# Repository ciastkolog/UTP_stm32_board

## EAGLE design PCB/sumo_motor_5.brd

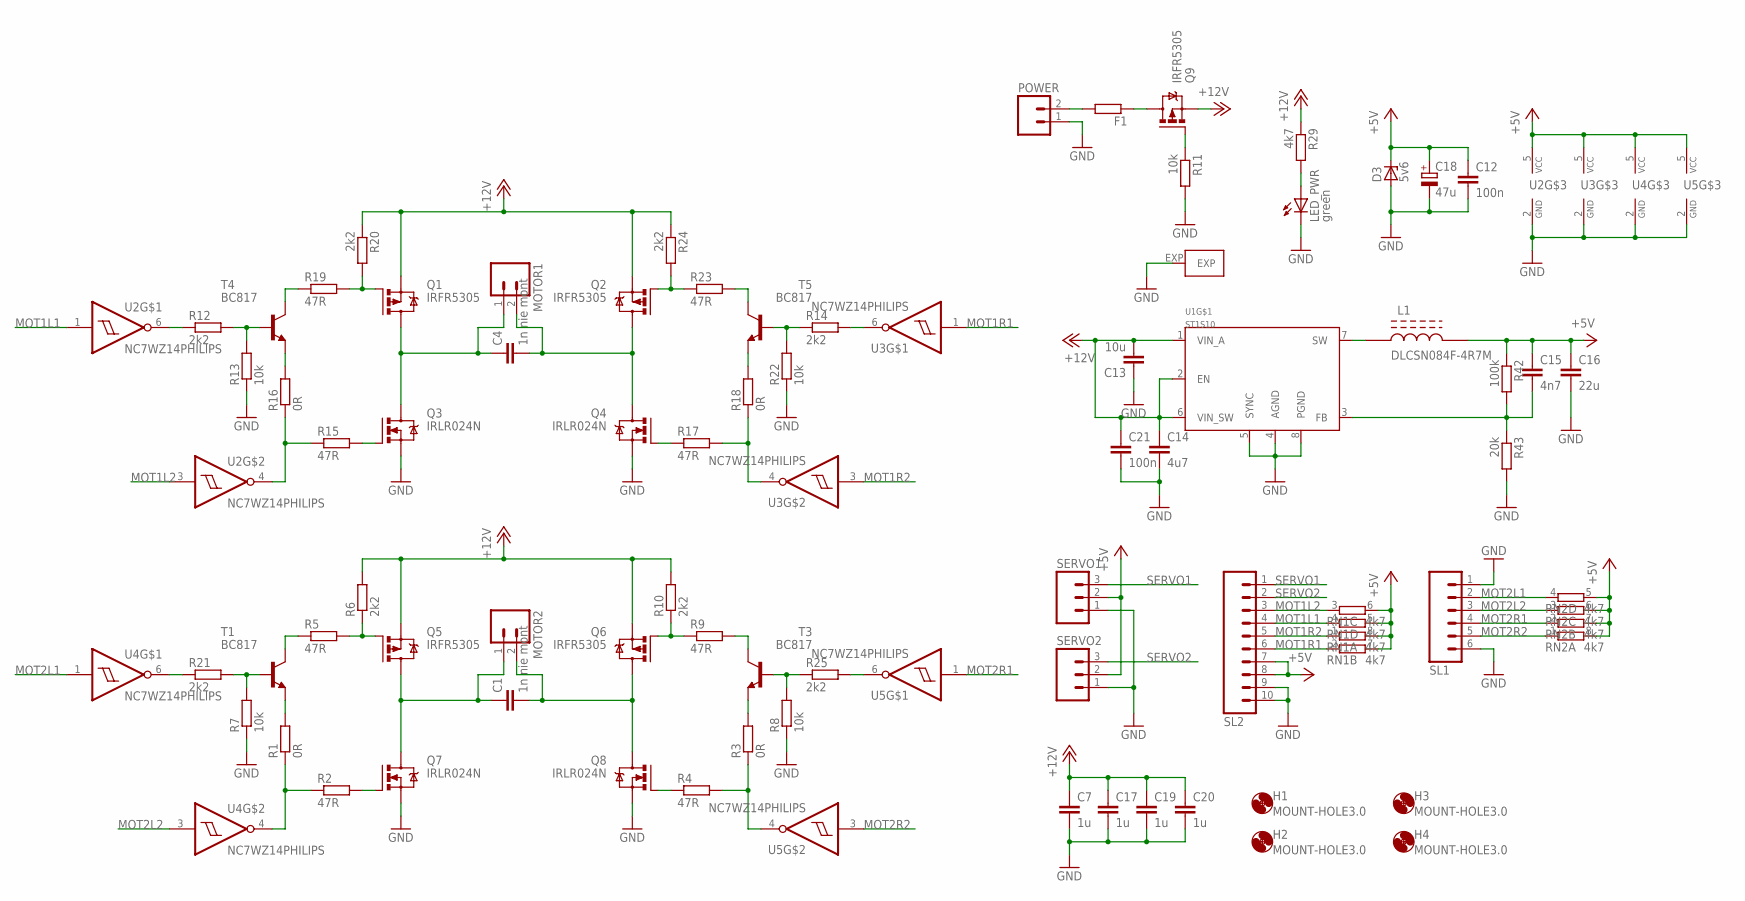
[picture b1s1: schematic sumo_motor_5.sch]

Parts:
C1, C4: 1n nie mont; C025-025X050
C7, C17, C19, C20: 1u; C0805
C12, C21: 100n; C0805
C13: 10u; C1206K
C14: 4u7; C0805
C15: 4n7; C0805
C16: 22u; C0805
C18: 47u; SMC_B
D3: 5v6; SMB
F1: R-EU_VMTA55; VMTA55
H1, H2, H3, H4: MOUNT-HOLE3.0; 3,0
L1: DLCSN084F-4R7M; CSN084F
LED_PWR: green; SML0805
MOTOR1, MOTOR2: M02; 02P
POWER: M02; 02P
Q1, Q2, Q5, Q6, Q9: IRFR5305; D-PAK_TO252AA
Q3, Q4, Q7, Q8: IRLR024N; D-PAK_TO252AA
R1, R3, R16, R18: 0R; R0603
R2, R4, R5, R9, R15, R17, R19, R23: 47R; R0603
R6, R10, R12, R14, R20, R21, R24, R25: 2k2; R0603
R7, R8, R11, R13, R22: 10k; R0603
R29: 4k7; R0603
R42: 100k; R0603
R43: 20k; R0603
RN1, RN2: 4k7; CAT16XXX
SERVO1, SERVO2: M03; 03P
SL1: M06; 06P
SL2: M10; 10P
T1, T3, T4, T5: BC817; SOT23-BEC
U1: ST1S10; HSOP8
U2, U3, U4, U5: NC7WZ14PHILIPS; SOT363_PHILIPS

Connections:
+5V: C12.1, C15.1, C16.1, C18.+, D3.C, L1.2, R42.1, RN1.5 (2), RN1.6 (2), RN1.7 (2), RN1.8 (2), RN2.5 (2), RN2.6 (2), RN2.7 (2), RN2.8 (2), SERVO1.2, SERVO2.2, SL2.7, SL2.8, U2.5 (VCC), U3.5 (VCC), U4.5 (VCC), U5.5 (VCC)
+12V: C7.1, C13.2, C14.1, C17.1, C19.1, C20.1, C21.1, Q1.3 (S), Q2.3 (S), Q5.3 (S), Q6.3 (S), Q9.3 (S), R6.2, R10.2, R20.1, R24.1, R29.1, U1.1 (VIN_A), U1.2 (EN), U1.6 (VIN_SW)
GND: C7.2, C12.2, C13.1, C14.2, C16.2, C17.2, C18.-, C19.2, C20.2, C21.2, D3.A, LED_PWR.C, POWER.1, Q3.3 (S), Q4.3 (S), Q7.3 (S), Q8.3 (S), R7.1, R8.1, R11.2, R13.1, R22.1, R43.2, SERVO1.1, SERVO2.1, SL1.1, SL1.6, SL2.9, SL2.10, U1.4 (AGND), U1.5 (SYNC), U1.8 (PGND), U1.EXP, U2.2 (GND), U3.2 (GND), U4.2 (GND), U5.2 (GND)
MOT1L1: RN1.4 (1), SL2.4, U2.1 (I)
MOT1L2: RN1.3 (1), SL2.3, U2.3 (I)
MOT1R1: RN1.2 (1), SL2.6, U3.1 (I)
MOT1R2: RN1.1, SL2.5, U3.3 (I)
MOT2L1: RN2.4 (1), SL1.2, U4.1 (I)
MOT2L2: RN2.3 (1), SL1.3, U4.3 (I)
MOT2R1: RN2.2 (1), SL1.4, U5.1 (I)
MOT2R2: RN2.1, SL1.5, U5.3 (I)
unnamed: R5.1, T1.C
unnamed: C1.1, MOTOR2.1, Q5.4 (D), Q7.4 (D)
unnamed: C1.2, MOTOR2.2, Q6.4 (D), Q8.4 (D)
unnamed: R19.1, T4.C
unnamed: R7.2, R21.2, T1.B
unnamed: Q5.1 (G), R5.2, R6.1
unnamed: Q6.1 (G), R9.1, R10.1
unnamed: R21.1, U4.6 (O)
unnamed: R1.2, T1.E
unnamed: R1.1, R2.1, U4.4 (O)
unnamed: Q3.1 (G), R15.2
unnamed: R16.2, T4.E
unnamed: Q7.1 (G), R2.2
unnamed: C4.1, MOTOR1.1, Q1.4 (D), Q3.4 (D)
unnamed: C4.2, MOTOR1.2, Q2.4 (D), Q4.4 (D)
unnamed: Q1.1 (G), R19.2, R20.2
unnamed: Q2.1 (G), R23.1, R24.2
unnamed: Q4.1 (G), R17.1
unnamed: R17.2, R18.1, U3.4 (O)
unnamed: R12.2, R13.2, T4.B
unnamed: R12.1, U2.6 (O)
unnamed: R18.2, T5.E
unnamed: R14.2, U3.6 (O)
unnamed: F1.2, POWER.2
unnamed: F1.1, Q9.4 (D)
unnamed: LED_PWR.A, R29.2
unnamed: Q8.1 (G), R4.1
unnamed: R3.1, R4.2, U5.4 (O)
unnamed: R3.2, T3.E
unnamed: R9.2, T3.C
unnamed: R8.2, R25.1, T3.B
unnamed: R25.2, U5.6 (O)
unnamed: L1.1, U1.7 (SW)
unnamed: C15.2, R42.2, R43.1, U1.3 (FB)
unnamed: Q9.1 (G), R11.1
unnamed: R23.2, T5.C
unnamed: R15.1, R16.1, U2.4 (O)
unnamed: R14.1, R22.2, T5.B
SERVO1: SERVO1.3, SL2.1
SERVO2: SERVO2.3, SL2.2

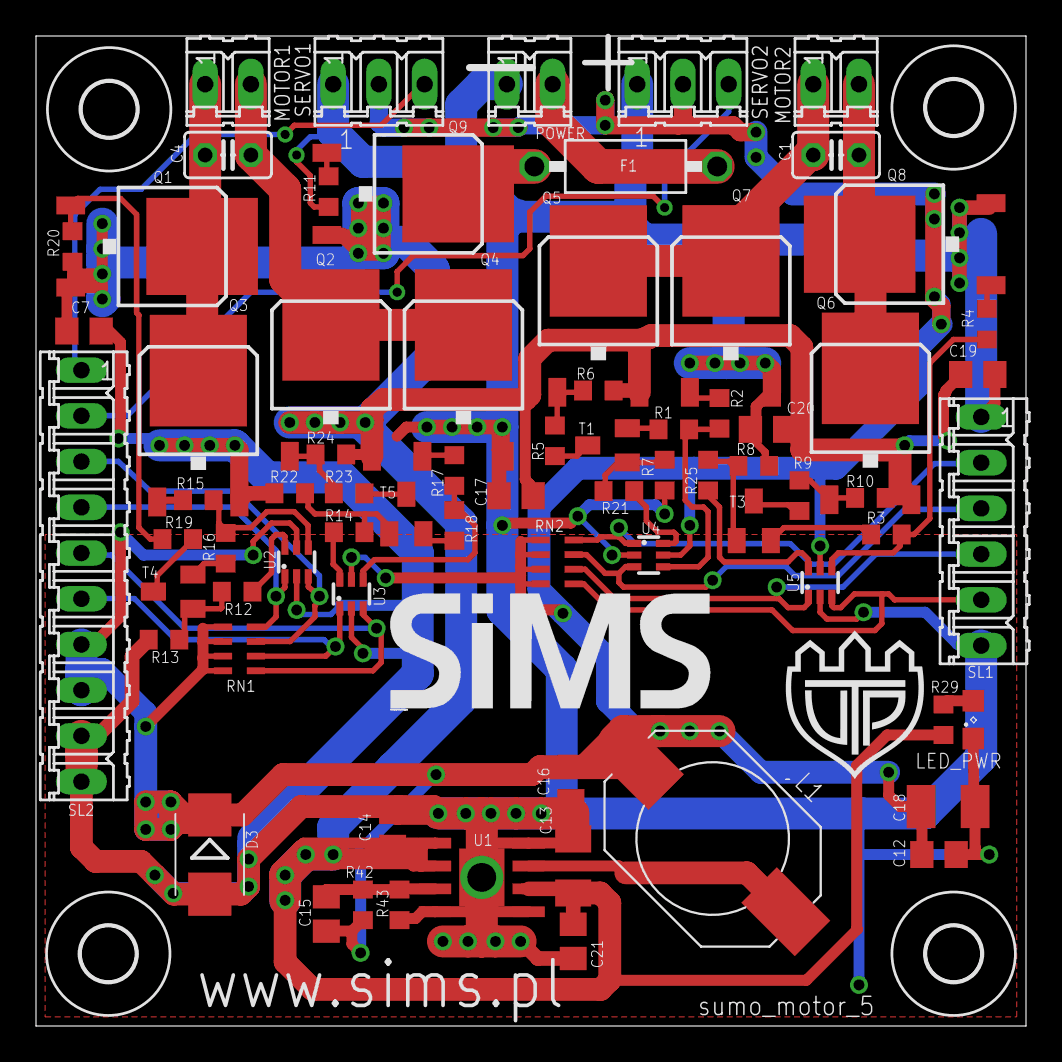
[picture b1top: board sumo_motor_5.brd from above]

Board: 2 copper layers, 55.0 x 55.0 mm, 78 parts (0 on the bottom side), 51 nets.

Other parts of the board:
U$1: SIMS_07
U$2: UTP_016

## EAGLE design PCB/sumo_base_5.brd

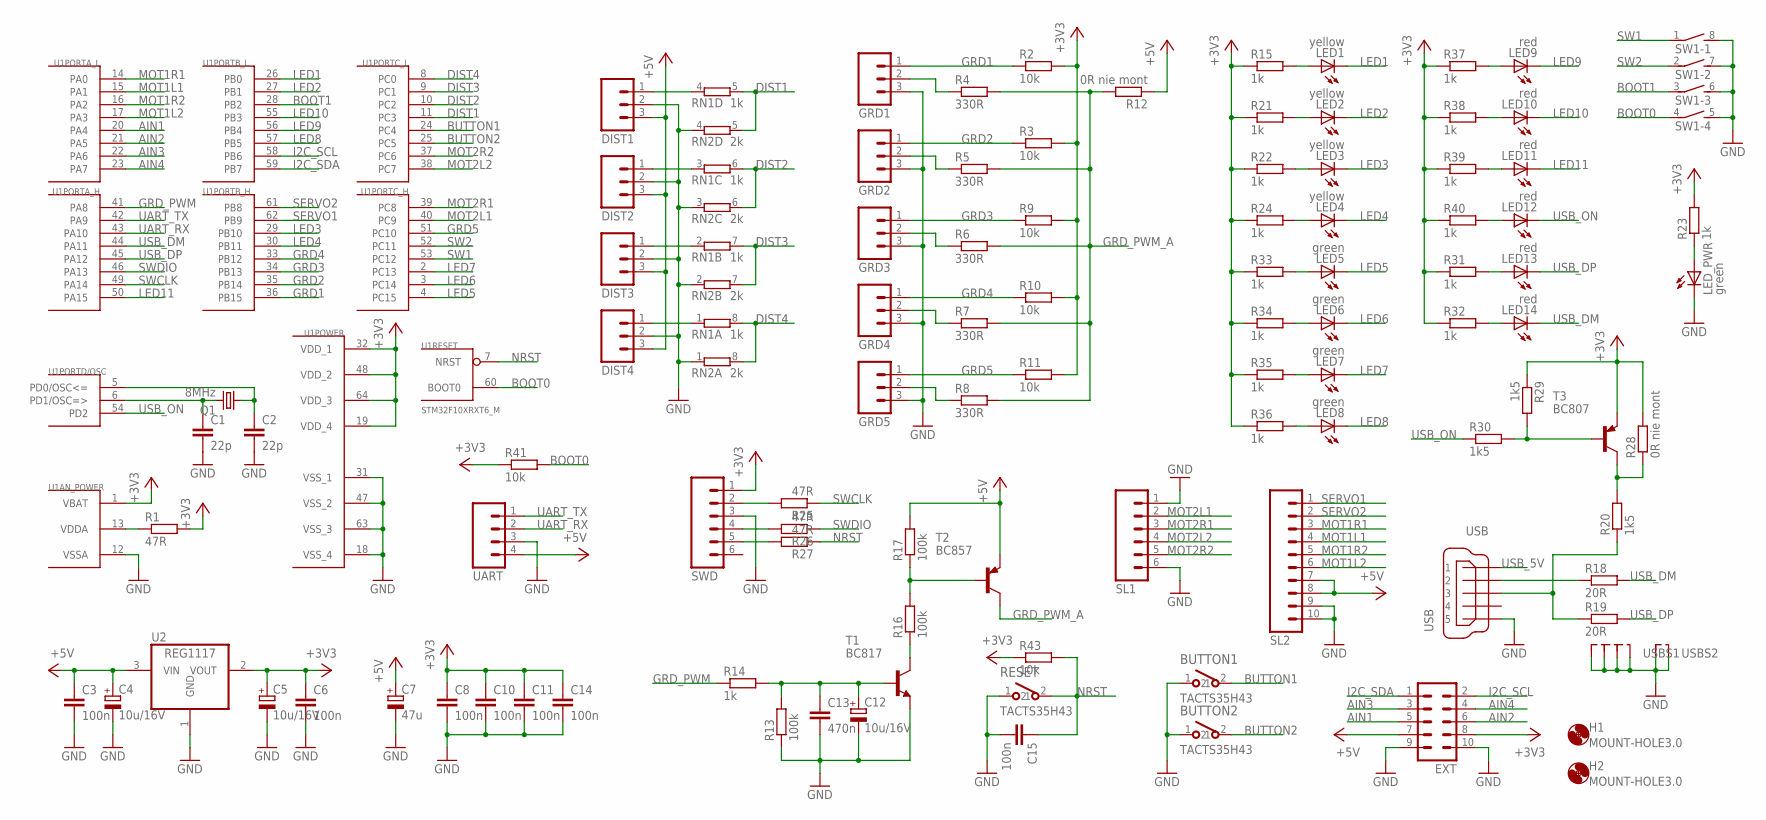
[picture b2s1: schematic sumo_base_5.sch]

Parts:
BUTTON1, BUTTON2: TACTS35H43
C1, C2: 22p; C0603
C3, C6, C8, C10, C11, C14, C15: 100n; C0603
C4, C5, C12: 10u/16V; SMC_A
C7: 47u; SMC_B
C13: 470n; C0603
DIST1, DIST2, DIST3, DIST4: M03; 03P
EXT: MA05-2
GRD1, GRD2, GRD3, GRD4, GRD5: M03; 03P
H1, H2: MOUNT-HOLE3.0; 3,0
LED1, LED2, LED3, LED4: yellow; SML0805
LED5, LED6, LED7, LED8: green; SML0805
LED9, LED10, LED11, LED12, LED13, LED14: red; SML0805
LED_PWR: green; SML0805
Q1: 8MHz; HC49/S
R1, R25, R26, R27: 47R; R0603
R2, R3, R9, R10, R11, R41, R43: 10k; R0603
R4, R5, R6, R7, R8: 330R; R0603
R12, R28: 0R nie mont; R0603
R13, R16, R17: 100k; R0603
R14, R15, R21, R22, R23, R24, R31, R32, R33, R34, R35, R36, R37, R38, R39, R40: 1k; R0603
R18, R19: 20R; R0603
R20, R29, R30: 1k5; R0603
RESET: TACTS35H43
RN1: 1k; CAT16XXX
RN2: 2k; CAT16XXX
SL1: M06; 06P
SL2: M10; 10P
SW1: DIP04S
SWD: M06; 06P
T1: BC817; SOT23-BEC
T2: BC857; SOT23-BEC
T3: BC807; SOT23-BEC
U1: STM32F10XRXT6_M; FP64E
U2: REG1117; SOT223
UART: M04; 04P
USB: USB; MX47346

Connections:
+3V3: C5.+, C6.1, C8.1, C10.1, C11.1, C14.1, EXT.8, R1.2, R2.2, R3.2, R9.2, R10.2, R11.2, R15.1, R21.1, R22.1, R23.2, R24.1, R28.2, R29.1, R31.1, R32.1, R33.1, R34.1, R35.1, R36.1, R37.1, R38.1, R39.1, R40.1, R41.1, R43.1, SWD.1, T3.E, U1.1 (VBAT), U1.19 (VDD_4), U1.32 (VDD_1), U1.48 (VDD_2), U1.64 (VDD_3), U2.2 (VOUT)
+5V: C3.1, C4.+, C7.+, DIST1.3, DIST2.3, DIST3.3, DIST4.3, EXT.7, R12.1, R17.2, SL2.7, SL2.8, T2.E, U2.3 (VIN), UART.4
AIN1: EXT.5, U1.20 (PA4)
AIN2: EXT.6, U1.21 (PA5)
AIN3: EXT.3, U1.22 (PA6)
AIN4: EXT.4, U1.23 (PA7)
BOOT0: R41.2, SW1.4 (1), U1.60 (BOOT0)
BOOT1: SW1.3 (1), U1.28 (PB2)
BUTTON1: BUTTON1.2, U1.24 (PC4)
BUTTON2: BUTTON2.2, U1.25 (PC5)
DIST1: RN1.5 (2), RN2.5 (2), U1.11 (PC3)
DIST2: RN1.6 (2), RN2.6 (2), U1.10 (PC2)
DIST3: RN1.7 (2), RN2.7 (2), U1.9 (PC1)
DIST4: RN1.8 (2), RN2.8 (2), U1.8 (PC0)
GND: BUTTON1.1, BUTTON2.1, C1.2, C2.2, C3.2, C4.-, C5.-, C6.2, C7.-, C8.2, C10.2, C11.2, C12.-, C13.2, C14.2, C15.2, DIST1.2, DIST2.2, DIST3.2, DIST4.2, EXT.9, EXT.10, GRD1.3, GRD2.3, GRD3.3, GRD4.3, GRD5.3, LED_PWR.C, R13.1, RESET.1, RN2.1, RN2.2 (1), RN2.3 (1), RN2.4 (1), SL1.1, SL1.6, SL2.9, SL2.10, SW1.5 (2), SW1.6 (2), SW1.7 (2), SW1.8 (2), SWD.3, T1.E, U1.12 (VSSA), U1.18 (VSS_4), U1.31 (VSS_1), U1.47 (VSS_2), U1.63 (VSS_3), U2.1 (GND), UART.3, USB.5, USB.M1 (S1), USB.M2 (S2), USB.M3 (S3), USB.M4 (S4), USB.M5 (S1), USB.M6 (S2)
GRD1: GRD1.1, R2.1, U1.36 (PB15)
GRD2: GRD2.1, R3.1, U1.35 (PB14)
GRD3: GRD3.1, R9.1, U1.34 (PB13)
GRD4: GRD4.1, R10.1, U1.33 (PB12)
GRD5: GRD5.1, R11.1, U1.51 (PC10)
GRD_PWM: R14.1, U1.41 (PA8)
GRD_PWM_A: R4.2, R5.2, R6.2, R7.2, R8.2, R12.2, T2.C
I2C_SCL: EXT.2, U1.58 (PB6)
I2C_SDA: EXT.1, U1.59 (PB7)
LED1: LED1.C, U1.26 (PB0)
LED2: LED2.C, U1.27 (PB1)
LED3: LED3.C, U1.29 (PB10)
LED4: LED4.C, U1.30 (PB11)
LED5: LED5.C, U1.4 (PC15)
LED6: LED6.C, U1.3 (PC14)
LED7: LED7.C, U1.2 (PC13)
LED8: LED8.C, U1.57 (PB5)
LED9: LED9.C, U1.56 (PB4)
LED10: LED10.C, U1.55 (PB3)
LED11: LED11.C, U1.50 (PA15)
MOT1L1: SL2.4, U1.15 (PA1)
MOT1L2: SL2.6, U1.17 (PA3)
MOT1R1: SL2.3, U1.14 (PA0)
MOT1R2: SL2.5, U1.16 (PA2)
MOT2L1: SL1.2, U1.40 (PC9)
MOT2L2: SL1.4, U1.38 (PC7)
MOT2R1: SL1.3, U1.39 (PC8)
MOT2R2: SL1.5, U1.37 (PC6)
unnamed: R29.2, R30.2, T3.B
unnamed: R20.2, R28.1, T3.C
unnamed: LED_PWR.A, R23.1
unnamed: LED12.A, R40.2
unnamed: LED13.A, R31.2
unnamed: LED14.A, R32.2
unnamed: R25.2, SWD.2
unnamed: C2.1, Q1.1, U1.5 (PD0/OSC<=)
unnamed: C1.1, Q1.2, U1.6 (PD1/OSC=>)
unnamed: R1.1, U1.13 (VDDA)
unnamed: DIST1.1, RN1.4 (1)
unnamed: GRD3.2, R6.1
unnamed: DIST3.1, RN1.2 (1)
unnamed: DIST2.1, RN1.3 (1)
unnamed: DIST4.1, RN1.1
unnamed: GRD1.2, R4.1
unnamed: GRD2.2, R5.1
unnamed: GRD4.2, R7.1
unnamed: GRD5.2, R8.1
unnamed: C12.+, C13.1, R13.2, R14.2, T1.B
unnamed: LED1.A, R15.2
unnamed: LED2.A, R21.2
unnamed: LED3.A, R22.2
unnamed: LED4.A, R24.2
unnamed: LED5.A, R33.2
unnamed: LED6.A, R34.2
unnamed: LED7.A, R35.2
unnamed: LED8.A, R36.2
unnamed: R16.1, T1.C
unnamed: R16.2, R17.1, T2.B
unnamed: R18.1, USB.2
unnamed: R19.1, R20.1, USB.3
unnamed: LED9.A, R37.2
unnamed: LED10.A, R38.2
unnamed: LED11.A, R39.2
unnamed: R26.2, SWD.4
unnamed: R27.2, SWD.5
NRST: C15.1, R27.1, R43.2, RESET.2, U1.7 (NRST)
SERVO1: SL2.1, U1.62 (PB9)
SERVO2: SL2.2, U1.61 (PB8)
SW1: SW1.1, U1.53 (PC12)
SW2: SW1.2 (1), U1.52 (PC11)
SWCLK: R25.1, U1.49 (PA14)
SWDIO: R26.1, U1.46 (PA13)
UART_RX: U1.43 (PA10), UART.2
UART_TX: U1.42 (PA9), UART.1
USB_5V: USB.1
USB_DM: LED14.C, R18.2, U1.44 (PA11)
USB_DP: LED13.C, R19.2, U1.45 (PA12)
USB_ON: LED12.C, R30.1, U1.54 (PD2)

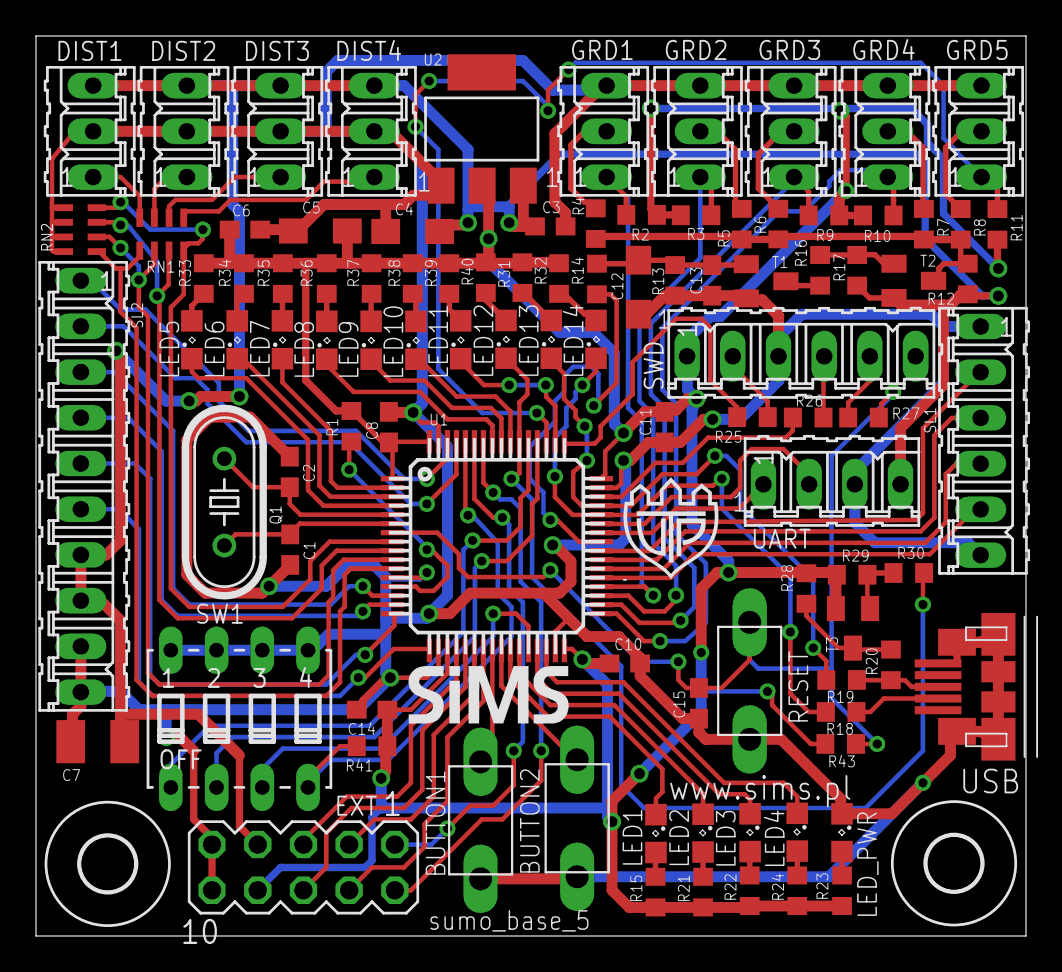
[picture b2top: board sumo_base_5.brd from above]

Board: 2 copper layers, 55.0 x 50.0 mm, 102 parts (0 on the bottom side), 92 nets.

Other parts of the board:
U$1: SIMS_035
U$2: UTP_011

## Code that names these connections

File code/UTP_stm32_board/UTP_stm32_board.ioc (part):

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Mcu.Name=STM32F103R(8-B)Tx
Mcu.Package=LQFP64
Mcu.UserName=STM32F103RBTx
PA10.Mode=Asynchronous
PA10.Signal=USART1_RX
PA13.Mode=Serial_Wire
PA13.Signal=SYS_JTMS-SWDIO
PA14.Mode=Serial_Wire
PA14.Signal=SYS_JTCK-SWCLK
PA15.GPIOParameters=PinState,GPIO_Label
PA15.GPIO_Label=LED11
PA15.PinState=GPIO_PIN_SET
PA15.Signal=GPIO_Output
PA9.Mode=Asynchronous
PA9.Signal=USART1_TX
PB0.GPIOParameters=PinState,GPIO_Label
PB0.GPIO_Label=LED1
PB0.PinState=GPIO_PIN_SET
PB0.Signal=GPIO_Output
PB1.GPIOParameters=PinState,GPIO_Label
PB1.GPIO_Label=LED2
PB1.PinState=GPIO_PIN_SET
PB1.Signal=GPIO_Output
PB10.GPIOParameters=PinState,GPIO_Label
PB10.GPIO_Label=LED3
PB10.PinState=GPIO_PIN_SET
PB10.Signal=GPIO_Output
PB11.GPIOParameters=PinState,GPIO_Label
PB11.GPIO_Label=LED4
PB11.PinState=GPIO_PIN_SET
PB11.Signal=GPIO_Output
PB2.GPIOParameters=GPIO_PuPd,GPIO_Label
PB2.GPIO_Label=SW3
PB2.GPIO_PuPd=GPIO_PULLUP
PB2.Signal=GPIO_Input
PB3.GPIOParameters=PinState,GPIO_Label
PB3.GPIO_Label=LED10
PB3.PinState=GPIO_PIN_SET
PB3.Signal=GPIO_Output
PB4.GPIOParameters=PinState,GPIO_Label
PB4.GPIO_Label=LED9
PB4.PinState=GPIO_PIN_SET
PB4.Signal=GPIO_Output
PB5.GPIOParameters=PinState,GPIO_Label
PB5.GPIO_Label=LED8
PB5.PinState=GPIO_PIN_SET
PB5.Signal=GPIO_Output
PC11.GPIOParameters=GPIO_PuPd,GPIO_Label
PC11.GPIO_Label=SW2
PC11.GPIO_PuPd=GPIO_PULLUP
PC11.Signal=GPIO_Input
PC12.GPIOParameters=GPIO_PuPd,GPIO_Label
PC12.GPIO_Label=SW1
PC12.GPIO_PuPd=GPIO_PULLUP
PC12.Signal=GPIO_Input
PC13-TAMPER-RTC.GPIOParameters=PinState,GPIO_Label
PC13-TAMPER-RTC.GPIO_Label=LED7
PC13-TAMPER-RTC.PinState=GPIO_PIN_SET
PC13-TAMPER-RTC.Signal=GPIO_Output
PC14-OSC32_IN.GPIOParameters=PinState,GPIO_Label
PC14-OSC32_IN.GPIO_Label=LED6
PC14-OSC32_IN.PinState=GPIO_PIN_SET
PC14-OSC32_IN.Signal=GPIO_Output
PC15-OSC32_OUT.GPIOParameters=PinState,GPIO_Label
PC15-OSC32_OUT.GPIO_Label=LED5
PC15-OSC32_OUT.PinState=GPIO_PIN_SET
PC15-OSC32_OUT.Signal=GPIO_Output
PC4.GPIOParameters=GPIO_PuPd,GPIO_Label
PC4.GPIO_Label=BUTTON1
PC4.GPIO_PuPd=GPIO_PULLUP
PC4.Signal=GPIO_Input
PC5.GPIOParameters=GPIO_PuPd,GPIO_Label
PC5.GPIO_Label=BUTTON2
PC5.GPIO_PuPd=GPIO_PULLUP
PC5.Signal=GPIO_Input
PD0-OSC_IN.Mode=HSE-External-Oscillator
PD0-OSC_IN.Signal=RCC_OSC_IN
PD1-OSC_OUT.Mode=HSE-External-Oscillator
PD1-OSC_OUT.Signal=RCC_OSC_OUT
PD2.GPIOParameters=PinState,GPIO_Label
PD2.GPIO_Label=USB_ON
PD2.PinState=GPIO_PIN_SET
PD2.Signal=GPIO_Output
RCC.SYSCLKFreq_VALUE=72000000
RCC.SYSCLKSource=RCC_SYSCLKSOURCE_PLLCLK
board=UTP_stm32_board

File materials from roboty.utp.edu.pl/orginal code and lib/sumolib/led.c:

/**
 * Funkcje obslugi diod LED, przyciskow i przelacznikow
 */

#include "stm32f10x.h"
#include "stm32f10x_gpio.h"
#include "stm32f10x_rcc.h"
#include "internal.h"

/**
 * Piny:
 * PB0 - LED1
 * PB1 - LED2
 * PB10 - LED3
 * PB11 - LED4
 * PC15 - LED5
 * PC14 - LED6
 * PC13 - LED7
 * PB5 - LED8
 * PB4 - LED9
 * PB3 - LED10
 * PA15 - LED11
 * PD2 - LED12 - USB_ON
 * PA12 - LED13 - USB_DP
 * PA11 - LED14 - USB_DM
 * PC4 - BUTTON1
 * PC5 - BUTTON2
 * PC12 - SW1
 * PC11 - SW2
 * PB2 - SW3 - BOOT1
 */

#define _LED_FIRST LED1
#if !_USB_ENABLE && _LED_EXT_ENABLE
#define _LED_LAST LED14
#else
#define _LED_LAST LED11
#endif

void switchLedInit() {
	// inicjalizacja portow przyciskow i przelacznikow
	GPIO_InitTypeDef GPIO_InitStructure;
	GPIO_InitStructure.GPIO_Speed = GPIO_Speed_50MHz;
	GPIO_InitStructure.GPIO_Mode = GPIO_Mode_IPU;
	GPIO_InitStructure.GPIO_Pin = GPIO_Pin_2;
	GPIO_Init(GPIOB, &GPIO_InitStructure);
	GPIO_InitStructure.GPIO_Pin = GPIO_Pin_4 | GPIO_Pin_5 | GPIO_Pin_11
			| GPIO_Pin_12;
	GPIO_Init(GPIOC, &GPIO_InitStructure);

	// wylaczenie pinow JTAGa
	GPIO_PinRemapConfig(GPIO_Remap_SWJ_JTAGDisable, ENABLE);

	// inicjalizacja portow diod LED
	GPIO_InitStructure.GPIO_Speed = GPIO_Speed_50MHz;
	GPIO_InitStructure.GPIO_Mode = GPIO_Mode_Out_PP;
	GPIO_InitStructure.GPIO_Pin = GPIO_Pin_15;
	GPIO_Init(GPIOA, &GPIO_InitStructure);
	GPIO_InitStructure.GPIO_Pin = GPIO_Pin_0 | GPIO_Pin_1 | GPIO_Pin_3
			| GPIO_Pin_4 | GPIO_Pin_5 | GPIO_Pin_10 | GPIO_Pin_11;
	GPIO_Init(GPIOB, &GPIO_InitStructure);
	GPIO_InitStructure.GPIO_Pin = GPIO_Pin_13 | GPIO_Pin_14 | GPIO_Pin_15;
	GPIO_Init(GPIOC, &GPIO_InitStructure);
#if !_USB_ENABLE && _LED_EXT_ENABLE
	GPIO_InitStructure.GPIO_Pin = GPIO_Pin_11 | GPIO_Pin_12;
	GPIO_Init(GPIOA, &GPIO_InitStructure);
	GPIO_InitStructure.GPIO_Pin = GPIO_Pin_2;
	GPIO_Init(GPIOD, &GPIO_InitStructure);
#endif
	// wygaszenie wszystkich
	int i;
	for (i = _LED_FIRST; i <= _LED_LAST; i++) {
		ledSet(i, LED_OFF);
	}
}

/**
 * Sprawdzenie czy przycisk jest nacisniety
 * buttonNumber - numer przycisku
 * zwraca 1 jesli tak, 0 jesli nie
 */
int buttonPressed(int buttonNumber) {
	switch (buttonNumber) {
	case BUTTON1:
		return !GPIO_ReadInputDataBit(GPIOC, GPIO_Pin_4);
	case BUTTON2:
		return !GPIO_ReadInputDataBit(GPIOC, GPIO_Pin_5);
	}
	return 0;
}

/**
 * Oczekiwanie na nacisniecie przycisku
 * buttonNumber - numer przycisku
 */
void waitForButton(int buttonNumber) {
	while (!buttonPressed(buttonNumber));
}

/**
 * Sprzwdzenie, czy przelacznik jest wlaczony
 * switchNumber - numer przelacznika
 * zwraca 1 jesli tak, 0 jesli nie
 */
int switchIsOn(int switchNumber) {
	switch (switchNumber) {
	case SWITCH1:
		return !GPIO_ReadInputDataBit(GPIOC, GPIO_Pin_12);
	case SWITCH2:
		return !GPIO_ReadInputDataBit(GPIOC, GPIO_Pin_11);
	case SWITCH3:
		return !GPIO_ReadInputDataBit(GPIOB, GPIO_Pin_2);
	}
	return 0;
}

/**
 * Zapalenie okreslonej diody
 * ledNumber - numer diody
 */
void ledOn(int ledNumber) {
	ledSet(ledNumber, LED_ON);
}

/**
 * Gaszenie okreslonej diody
 * ledNumber - numer diody
 */
void ledOff(int ledNumber) {
	ledSet(ledNumber, LED_OFF);
}

/**
 * Ustawienie stanu okreslonej diody
 * ledNumber - numer diody
 * ledState - stan diody 0 - zgaszona, 1 - zapalona
 */
void ledSet(int ledNumber, int ledState) {
	switch (ledNumber) {
	case LED1:
		GPIO_WriteBit(GPIOB, GPIO_Pin_0, !ledState);
		break;
	case LED2:
		GPIO_WriteBit(GPIOB, GPIO_Pin_1, !ledState);
		break;
	case LED3:
		GPIO_WriteBit(GPIOB, GPIO_Pin_10, !ledState);
		break;
	case LED4:
		GPIO_WriteBit(GPIOB, GPIO_Pin_11, !ledState);
		break;
	case LED5:
		GPIO_WriteBit(GPIOC, GPIO_Pin_15, !ledState);
		break;
	case LED6:
		GPIO_WriteBit(GPIOC, GPIO_Pin_14, !ledState);
		break;
	case LED7:
		GPIO_WriteBit(GPIOC, GPIO_Pin_13, !ledState);
		break;
	case LED8:
		GPIO_WriteBit(GPIOB, GPIO_Pin_5, !ledState);
		break;
	case LED9:
		GPIO_WriteBit(GPIOB, GPIO_Pin_4, !ledState);
		break;
	case LED10:
		GPIO_WriteBit(GPIOB, GPIO_Pin_3, !ledState);
		break;
	case LED11:
		GPIO_WriteBit(GPIOA, GPIO_Pin_15, !ledState);
		break;
#if !_USB_ENABLE && _LED_EXT_ENABLE
		case LED12:
		GPIO_WriteBit(GPIOD, GPIO_Pin_2, !ledState);
		break;
		case LED13:
		GPIO_WriteBit(GPIOA, GPIO_Pin_12, !ledState);
		break;
		case LED14:
		GPIO_WriteBit(GPIOA, GPIO_Pin_11, !ledState);
		break;
#endif
	}

}

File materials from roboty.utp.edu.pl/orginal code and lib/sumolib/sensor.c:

/**
 * Funkcje obslugi czujnikow
 */
#include "stm32f10x.h"
#include "stm32f10x_gpio.h"
#include "stm32f10x_rcc.h"
#include "stm32f10x_tim.h"
#include "stm32f10x_adc.h"
#include "stm32f10x_dma.h"
#include "internal.h"
/**
 * Piny:
 * PC3 - DIST1 - IN13
 * PC2 - DIST2 - IN12
 * PC1 - DIST3 - IN11
 * PC0 - DIST4 - IN10
 * PA4 - AIN1 - IN4
 * PA5 - AIN2 - IN3
 * PA6 - AIN3 - IN2
 * PA7 - AIN4 - IN1
 * PB15 - GRD1
 * PB14 - GRD2
 * PB13 - GRD3
 * PB12 - GRD4
 * PC10 - GRD5
 * PA8- GRD_PWM - TIM1_CH1
 */
#define ADC1_DR_Address    ((uint32_t)0x4001244C)
#if _USE_EXT_DIST
#define _CHANNEL_NUMBER 8
#else
#define _CHANNEL_NUMBER 4
#endif
// wartosci pomiarow
__IO uint16_t distValues[_CHANNEL_NUMBER];
// czulosc czujnikow w %
__IO uint8_t grdSensivity = 100;
// licznik na potrzeby programowego PWMa
__IO uint16_t grdSensCounter = 0;

void sensorInit() {

	// konfiguracja portow - DIST
	GPIO_InitTypeDef GPIO_InitStructure;
	GPIO_InitStructure.GPIO_Mode = GPIO_Mode_AIN;
	GPIO_InitStructure.GPIO_Pin = GPIO_Pin_0 | GPIO_Pin_1 | GPIO_Pin_2
			| GPIO_Pin_3;
	GPIO_Init(GPIOC, &GPIO_InitStructure);
#if _DIST_EXT_ENABLE
	GPIO_InitStructure.GPIO_Pin = GPIO_Pin_4 | GPIO_Pin_5 | GPIO_Pin_6 | GPIO_Pin_7;
	GPIO_Init(GPIOA, &GPIO_InitStructure);
#endif

	// konfiguracja DMA
	DMA_DeInit(DMA1_Channel1);
	DMA_InitTypeDef DMA_InitStructure;
	DMA_InitStructure.DMA_PeripheralBaseAddr = ADC1_DR_Address;
	DMA_InitStructure.DMA_MemoryBaseAddr = (uint32_t) & distValues;
	DMA_InitStructure.DMA_DIR = DMA_DIR_PeripheralSRC;
	DMA_InitStructure.DMA_BufferSize = _CHANNEL_NUMBER;
	DMA_InitStructure.DMA_PeripheralInc = DMA_PeripheralInc_Disable;
	DMA_InitStructure.DMA_MemoryInc = DMA_MemoryInc_Enable;
	DMA_InitStructure.DMA_PeripheralDataSize = DMA_PeripheralDataSize_HalfWord;
	DMA_InitStructure.DMA_MemoryDataSize = DMA_MemoryDataSize_HalfWord;
	DMA_InitStructure.DMA_Mode = DMA_Mode_Circular;
	DMA_InitStructure.DMA_Priority = DMA_Priority_High;
	DMA_InitStructure.DMA_M2M = DMA_M2M_Disable;
	DMA_Init(DMA1_Channel1, &DMA_InitStructure);
	DMA_Cmd(DMA1_Channel1, ENABLE);

	// konfiguracja ADC
	ADC_InitTypeDef ADC_InitStructure;
	ADC_InitStructure.ADC_Mode = ADC_Mode_Independent;
	ADC_InitStructure.ADC_ScanConvMode = ENABLE;
	ADC_InitStructure.ADC_ContinuousConvMode = ENABLE;
	ADC_InitStructure.ADC_ExternalTrigConv = ADC_ExternalTrigConv_None;
	ADC_InitStructure.ADC_DataAlign = ADC_DataAlign_Right;
	ADC_InitStructure.ADC_NbrOfChannel = _CHANNEL_NUMBER;
	ADC_Init(ADC1, &ADC_InitStructure);

	ADC_RegularChannelConfig(ADC1, ADC_Channel_13, 1, ADC_SampleTime_55Cycles5);
	ADC_RegularChannelConfig(ADC1, ADC_Channel_12, 2, ADC_SampleTime_55Cycles5);
	ADC_RegularChannelConfig(ADC1, ADC_Channel_11, 3, ADC_SampleTime_55Cycles5);
	ADC_RegularChannelConfig(ADC1, ADC_Channel_10, 4, ADC_SampleTime_55Cycles5);
#if _DIST_EXT_ENABLE
	ADC_RegularChannelConfig(ADC1, ADC_Channel_4, 5, ADC_SampleTime_55Cycles5);
	ADC_RegularChannelConfig(ADC1, ADC_Channel_3, 6, ADC_SampleTime_55Cycles5);
	ADC_RegularChannelConfig(ADC1, ADC_Channel_2, 7, ADC_SampleTime_55Cycles5);
	ADC_RegularChannelConfig(ADC1, ADC_Channel_1, 8, ADC_SampleTime_55Cycles5);
#endif

	// uruchomienie przetwarzania
	ADC_DMACmd(ADC1, ENABLE);
	ADC_Cmd(ADC1, ENABLE);
	ADC_ResetCalibration(ADC1);
	while (ADC_GetResetCalibrationStatus(ADC1))
		;
	ADC_StartCalibration(ADC1);
	while (ADC_GetCalibrationStatus(ADC1))
		;
	ADC_SoftwareStartConvCmd(ADC1, ENABLE);

	// konfiguracja portow - GRD
	GPIO_InitStructure.GPIO_Speed = GPIO_Speed_50MHz;
	GPIO_InitStructure.GPIO_Mode = GPIO_Mode_IPU;
	GPIO_InitStructure.GPIO_Pin = GPIO_Pin_12 | GPIO_Pin_13 | GPIO_Pin_14
			| GPIO_Pin_15;
	GPIO_Init(GPIOB, &GPIO_InitStructure);
	GPIO_InitStructure.GPIO_Pin = GPIO_Pin_10;
	GPIO_Init(GPIOC, &GPIO_InitStructure);
	GPIO_InitStructure.GPIO_Mode = GPIO_Mode_Out_PP;
	GPIO_InitStructure.GPIO_Pin = GPIO_Pin_8;
	GPIO_Init(GPIOA, &GPIO_InitStructure);
	GPIO_SetBits(GPIOA, GPIO_Pin_8);
}

/**
 * Pobranie wartosci czujnika w mv
 * distNumber - numer czujnika
 */
int distValue(int distNumber) {
	int value = 0;
	switch (distNumber) {
	case DIST1:
		value = distValues[0];
		break;
	case DIST2:
		value = distValues[1];
		break;
	case DIST3:
		value = distValues[2];
		break;
	case DIST4:
		value = distValues[3];
		break;
#if _DIST_EXT_ENABLE
		case DIST5:
		value = distValues[4];
		break;
		case DIST6:
		value = distValues[5];
		break;
		case DIST7:
		value = distValues[6];
		break;
		case DIST8:
		value = distValues[7];
		break;
#endif
	}
	return (value * 807L) / 1000;
}

/**
 * Sprawdzenie, czy czujnik widzi biala linie
 * grdNumber - numer czujnika
 */
int grdDetected(int grdNumber) {
	switch (grdNumber) {
	case GRD1:
		return !GPIO_ReadInputDataBit(GPIOB, GPIO_Pin_15);
	case GRD2:
		return !GPIO_ReadInputDataBit(GPIOB, GPIO_Pin_14);
	case GRD3:
		return !GPIO_ReadInputDataBit(GPIOB, GPIO_Pin_13);
	case GRD4:
		return !GPIO_ReadInputDataBit(GPIOB, GPIO_Pin_12);
	case GRD5:
		return !GPIO_ReadInputDataBit(GPIOC, GPIO_Pin_10);
	}
	return 0;
}

/**
 * Ustawienie czulosci czujnikow, w zakresie 0-100%
 * sensivity czulosc
 */
void grdSetSensivity(int sensivity) {
	if (sensivity < 0) {
		sensivity = 0;
	} else if (sensivity > 100) {
		sensivity = 100;
	}
	grdSensivity = sensivity;
}

void sensorSystickInterrupt() {
	// programowy PWM do jasnosci diod czujnikow podloza
	grdSensCounter++;
	// przelaczanie
	if (grdSensivity < 100) {
		if (grdSensCounter * 100
				== (_SYSTICK_FREQUENCY / _GRD_PWM_FREQUENCY) * grdSensivity) {
			GPIO_ResetBits(GPIOA, GPIO_Pin_8);
		}
	}
	// sprawdzanie czy nie nastapilo przepelnienie
	if (grdSensCounter >= _SYSTICK_FREQUENCY / _GRD_PWM_FREQUENCY) {
		grdSensCounter = 0;
		GPIO_SetBits(GPIOA, GPIO_Pin_8);
	}
}

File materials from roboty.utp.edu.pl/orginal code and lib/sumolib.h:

/**
 * Plik naglowkowy biblioteki
 */

#ifndef _SUMOLIB
#define _SUMOLIB 1 // wersja biblioteki

#include "sumoconf.h"

// deklaracje funkcji

// -------------------- Util --------------------

/**
 * Inicjalizacja procesora
 */
void init();

/**
 * Oczekiwanie okreslonej ilosci milisekund
 */
void waitMs(int ms);

/**
 * Oczekiwanie okreslonej ilosci sekund
 */
void wait(int s);

/**
 * Wartosc pseudolosowa
 * range - zakres wartosci
 */
int randomValue(int range);

/**
 * Ilosc milisekund od startu programu
 */
int timeInMilis();

// ------------------------- Switch & Led -------------------------

// definicja przyciskow i przelacznikow
#define BUTTON1 1
#define BUTTON2 2
#define SWITCH1 1
#define SWITCH2 2
#define SWITCH3 3

// definicje diod
#define LED1 1
#define LED2 2
#define LED3 3
#define LED4 4
#define LED5 5
#define LED6 6
#define LED7 7
#define LED8 8
#define LED9 9
#define LED10 10
#define LED11 11
#if !_USB_ENABLE && _LED_EXT_ENABLE
#define LED12 12
#define LED13 13
#define LED14 14
#endif
#define LED_ON 1
#define LED_OFF 0

/**
 * Sprawdzenie czy przycisk jest nacisniety
 * buttonNumber - numer przycisku
 * zwraca 1 jesli tak, 0 jesli nie
 */
int buttonPressed(int buttonNumber);

/**
 * Oczekiwanie na nacisniecie przycisku
 * buttonNumber - numer przycisku
 */
void waitForButton(int buttonNumber);

/**
 * Sprzwdzenie, czy przelacznik jest wlaczony
 * switchNumber - numer przelacznika
 * zwraca 1 jesli tak, 0 jesli nie
 */
int switchIsOn(int switchNumber);

/**
 * Zapalenie okreslonej diody
 * ledNumber - numer diody
 */
void ledOn(int ledNumber);

/**
 * Gaszenie okreslonej diody
 * ledNumber - numer diody
 */
void ledOff(int ledNumber);

/**
 * Ustawienie stanu okreslonej diody
 * ledNumber - numer diody
 * ledState - stan diody 0 - zgaszona, 1 - zapalona
 */
void ledSet(int ledNumber, int ledState);

// ------------------------- Sensor -------------------------

// definicje czujnikow
#define DIST1 1
#define DIST2 2
#define DIST3 3
#define DIST4 4
#if _DIST_EXT_ENABLE
#define DIST5 5
#define DIST6 6
#define DIST7 7
#define DIST8 8
#endif
#define GRD1 1
#define GRD2 2
#define GRD3 3
#define GRD4 4
#define GRD5 5

/**
 * Pobranie wartosci czujnika w mv
 * distNumber - numer czujnika
 */
int distValue(int distNumber);

/**
 * Sprawdzenie, czy czujnik widzi biala linie
 * grdNumber - numer czujnika
 */
int grdDetected(int grdNumber);

/**
 * Ustawienie czulosci czujnikow, w zakresie 0-100%
 * sensivity czulosc
 */
void grdSetSensivity(int sensivity);

// ------------------------- Motor -------------------------

// definicje silnikow
#define MOTOR1 1
#define MOTOR2 2

/**
 * Ruch silnika do przodu
 * motorNumber - numer silnika
 */
void motorForward(int motorNumber);

/**
 * Ruch silnika do tylu
 * motorNumber - numer silnika
 */
void motorBackward(int motorNumber);

/**
 * Zatrzymanie silnika
 * motorNumber - numer silnika
 */
void motorStop(int motorNumber);

/**
 * Hamowanie silnikiem
 * motorNumber - numer silnika
 */
void motorBreak(int motorNumber);

/**
 * Ustawia moc (wypelnienie) silnika
 * motorNumber - numer silnika
 * power - moc w % (0-100)
 */
void motorSetPower(int motorNumber, int power);

// ------------------------- Servo -------------------------

// definicje serwomechanizmow
#define SERVO1 1
#define SERVO2 2

/**
 * Ustawia zadany kat wychylenia serwa
 * servoNumber - numer serwa
 * angle - kat o - 180 stopni
 */
void servoSetAngle(int servoNumber, int angle);

/**
 * Ruch do przodu
 * Uzywac tylko jesli jako naped jest zastosowany przerobiony serwomechanizm
 */
void servoForward(int servoNumber);

/**
 * Ruch do tylu
 * Uzywac tylko jesli jako naped jest zastosowany przerobiony serwomechanizm
 */
void servoBackward(int servoNumber);

/**
 * Zatrzymanie serwomechanizmu
 */
void servoStop(int servoNumber);

// -------------------- Util --------------------

/**
 * Planuje jednorazowe wywolanie funkcji
 * timerFunction - funkcja do wywolania
 * delay - czas za jaki funkcja ma byc wywolana
 */
void timerScheduleOnce(void (*timerFunction)(void), int delay);

/**
 * Planuje cykliczne wywolywanie funkcji
 * timerFunction - funkcja do wywolania
 * period - czas co jaki funkcja ma byc wywolana
 */
void timerSchedule(void (*timerFunction)(void), int period);

/**
 * Anulowanie wywolywania funkcji
 */
void timerCancel(void (*timerFunction)(void));


// -------------------- USART --------------------
#if _USART_ENABLE

/**
 * Wysyla znak na port szeregwy
 */
void usartSendChar(char c);

/**
 * Wysyla zawartosc bufora na port szeregowy
 * buff - dlugosc bufora
 * len - ilosc bajtw do wyslania
 */
void usartSendRaw(char* buff, int len);

/**
 * Wysyla tekst na port szeregowy
 */
void usartWrite(char* str);

/**
 * Zwraca 1 jesli sa dane odebrane z portu szeregowego
 */
int usartHasData();

/**
 * Zwraca pojedynczy znak odebrany z portu szeregowego
 */
char usartGetChar();

/**
 * zapisuje w buforze linijke tekstu odebrana z portu seregowego
 * buf - bufor do ktorego beda zapisane dane
 * zwraca ilosc danych
 */
int usartReadLine(char *buff);

#endif

// -------------------- rprintf --------------------

#if _RPRINTF_ENABLE
/**
 * Odpowiednik funkcji printf z C
 */
int rprintf(const char *format, ...);

/**
 * Odpowiednik funkcji sprintf z C
 */
int rsprintf(char *buffer, const char *format, ...);
#endif

#if _RSCANF_ENABLE
/**
 * Odpowiednik funkcji scanf z C
 */
int rscanf(const char* format, ...);
#endif

#endif // _SUMOLIB

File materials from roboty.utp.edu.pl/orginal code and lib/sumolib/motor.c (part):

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
/**
 * Piny:
 * PA0 - MOT1_R1 - TIM2_CH1
 * PA1 - MOT1_L1 - TIM2_CH2
 * PA2 - MOT1_R2 - TIM2_CH3
 * PA3 - MOT1_L2 - TIM2_CH4
 * PC6 - MOT2_R2 - TIM3_CH1 Remap
 * PC7 - MOT2_L2 - TIM3_CH2 Remap
 * PC8 - MOT2_R1 - TIM3_CH3 Remap
 * PC9 - MOT2_L1 - TIM3_CH4 Remap
 */

// funkcje lokalne
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
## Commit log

2017-11-10 Blank project with preconfigure pins
    Atolic+CubeMX
2017-11-10 Add scheme and PCB project
2017-11-10 Add materials from roboty.utp.edu.pl
2017-11-10 Add scheme in png format
2017-11-18 test
